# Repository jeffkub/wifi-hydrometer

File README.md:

# wifi-hydrometer
A WiFi-enabled hydrometer and temperature sensor using a ESP8266.  Concept taken from [iSpindel](https://github.com/universam1/iSpindel) and miniturized to fit inside a standard size soda bottle perform.

# Licensing
Design is based on the Adafruit Feather ESP8266 HUZZAH.  
For more details, check out the product page at

  * https://www.adafruit.com/product/2821

Adafruit invests time and resources providing this open source design, 
please support Adafruit and open-source hardware by purchasing 
products from Adafruit!

Adapted from a design by Adafruit Industries.  
Creative Commons Attribution, Share-Alike license, check license.txt for more information
All text above must be included in any redistribution

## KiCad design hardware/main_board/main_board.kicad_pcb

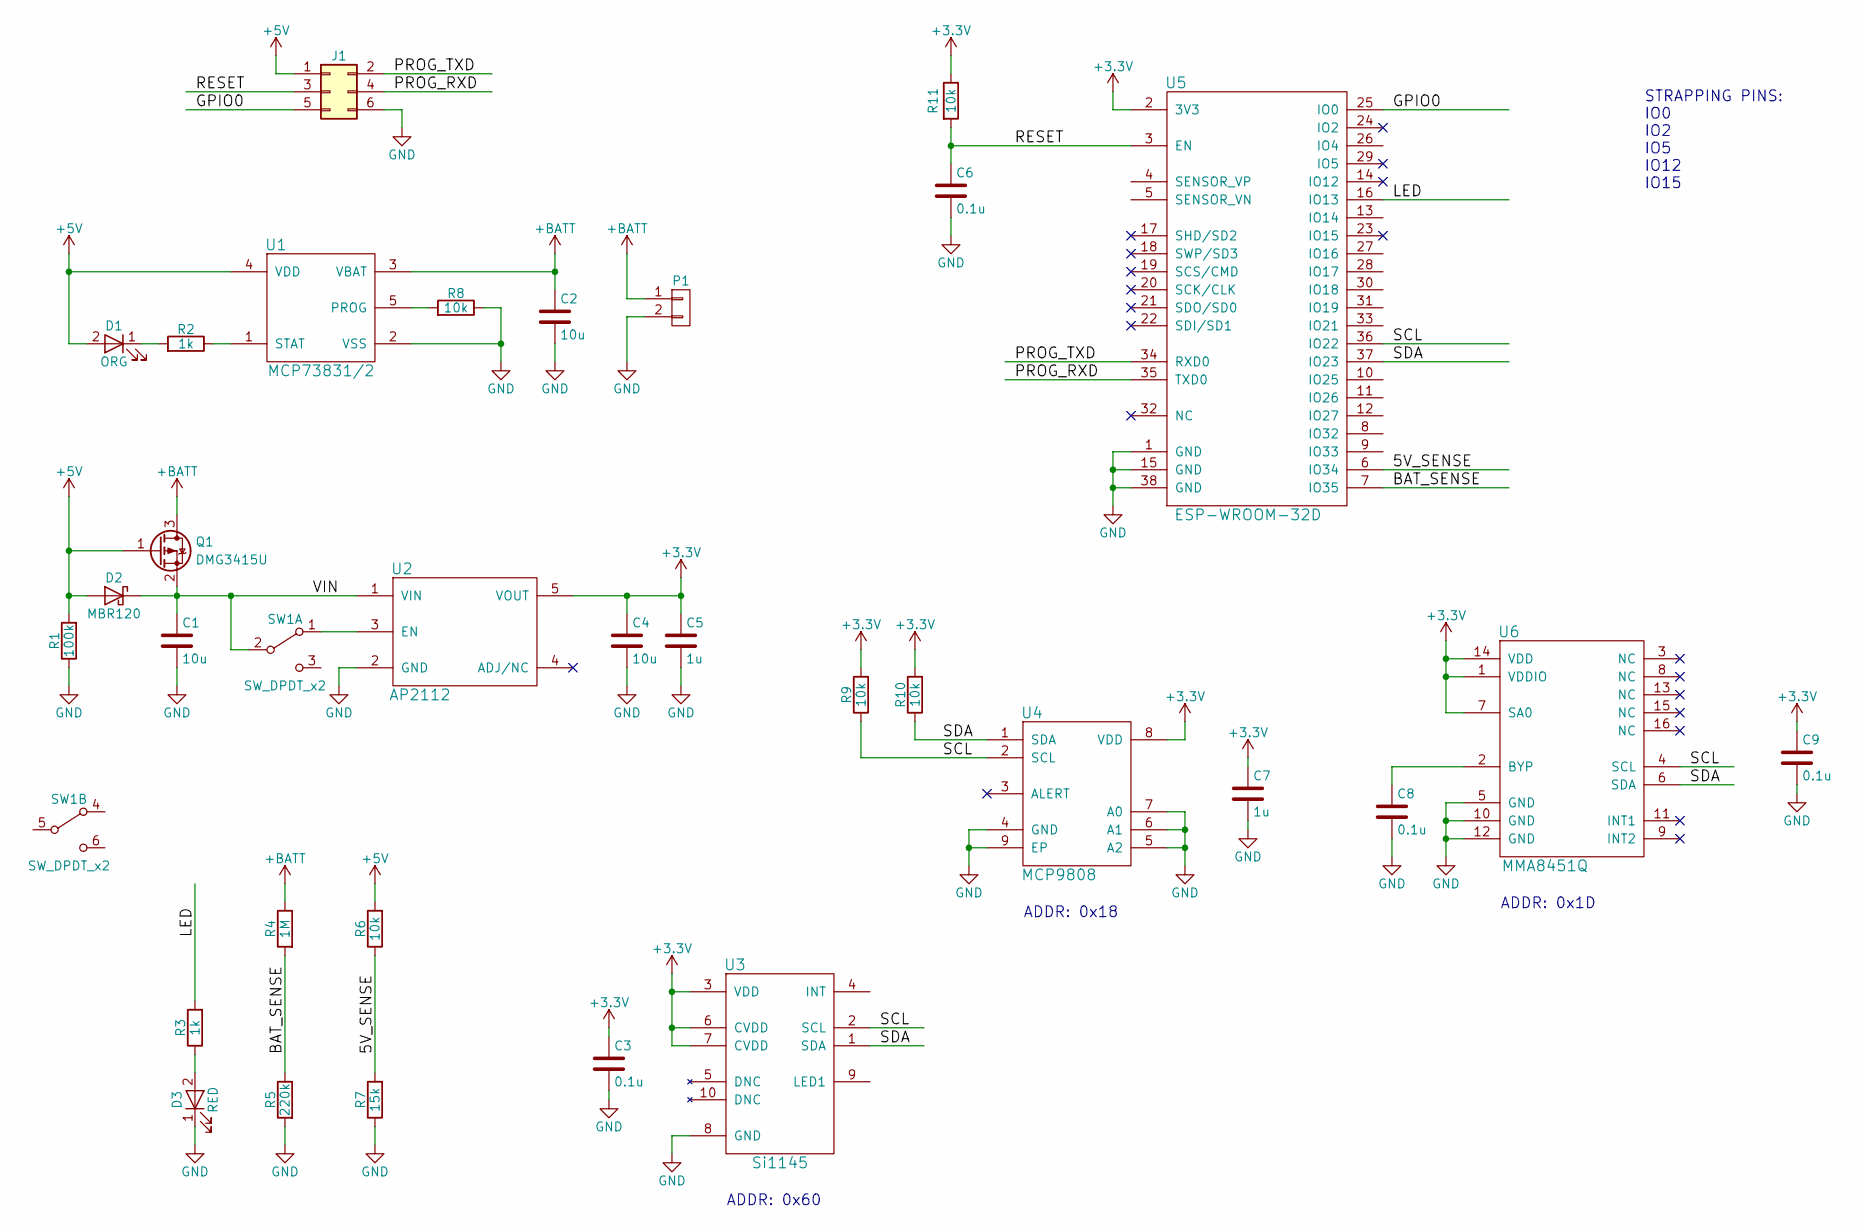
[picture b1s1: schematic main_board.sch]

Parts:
C1, C2, C4: 10u; C_0805; Part 311-1460-1-ND
C3, C6, C8, C9: 0.1u; C_0603; Part 311-1344-1-ND
C5, C7: 1u; C_0603; Part 311-1444-1-ND
D1: ORG; LED_0603; Part 160-1434-1-ND
D2: MBR120; SOD-123FL; Part MBR120VLSFT3GOSCT-ND
D3: RED; LED_0603; Part 160-1447-1-ND
J1: eConn_02x03_Odd_Even; Socket_Strip_Angled_2x03_Pitch2.54mm; Part S5556-ND
P1: CONN_01X02; S2B-PH-SM4-TB(LF)(SN); Part 455-1749-1-ND
Q1: DMG3415U; SOT-23; Part DMG3415UDICT-ND
R1: 100k; R_0603; Part 311-100KHRCT-ND
R2, R3: 1k; R_0603; Part 311-1.00KHRCT-ND
R4: 1M; R_0603; Part 311-1.00MHRCT-ND
R5: 220k; R_0603; Part 311-220KHRCT-ND
R6, R8, R9, R10, R11: 10k; R_0603; Part 311-10.0KHRCT-ND
R7: 15k; R_0603; Part 311-15.0KHRCT-ND
SW1: SW_DPDT_x2; CL-SB-22A; Part 563-1340-1-ND
U1: MCP73831/2; SOT-23-5; Part MCP73831T-2ACI/OTCT-ND
U2: AP2112; SOT-23-5; Part AP2112K-3.3TRG1DICT-ND
U3: Si1145; Part 336-2622-1-ND
U4: MCP9808; DFN-8-1EP_3x2mm_Pitch0.5mm; Part MCP9808T-E/MCCT-ND
U5: ESP-WROOM-32D; ESP32-WROOM; Part 1528-1801-ND
U6: MMA8451Q; Part MMA8451QR1CT-ND

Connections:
+3V3: C3.1, C4.1, C5.1, C7.1, C9.1, R9.2, R10.2, R11.1, U2.5 (VOUT), U3.3 (VDD), U3.6 (CVDD), U3.7 (CVDD), U4.8 (VDD), U5.2 (3V3), U6.1 (VDDIO), U6.7 (SA0), U6.14 (VDD)
+5V: D1.2 (A), D2.2 (A), J1.1, Q1.1 (G), R1.2, R6.2, U1.4 (VDD)
+BATT: C2.1, P1.1, Q1.3 (D), R4.1, U1.3 (VBAT)
/5V_SENSE: R6.1, R7.2, U5.6 (IO34)
/BAT_SENSE: R4.2, R5.1, U5.7 (IO35)
/GPIO0: J1.5, U5.25 (IO0)
/LED: R3.2, U5.16 (IO13)
/PROG_RXD: J1.4, U5.35 (TXD0)
/PROG_TXD: J1.2, U5.34 (RXD0)
/RESET: C6.1, J1.3, R11.2, U5.3 (EN)
/SCL: R9.1, U3.2 (SCL), U4.2 (SCL), U5.36 (IO22), U6.4 (SCL)
/SDA: R10.1, U3.1 (SDA), U4.1 (SDA), U5.37 (IO23), U6.6 (SDA)
/VIN: C1.1, D2.1 (K), Q1.2 (S), SW1.2 (B), U2.1 (VIN)
GND: C1.2, C2.2, C3.2, C4.2, C5.2, C6.2, C7.2, C8.2, C9.2, D3.1 (K), J1.6, P1.2, R1.1, R5.2, R7.1, R8.1, U1.2 (VSS), U2.2 (GND), U3.8 (GND), U4.4 (GND), U4.5 (A2), U4.6 (A1), U4.7 (A0), U4.9 (EP), U5.1 (GND), U5.15 (GND), U5.38 (GND), U6.5 (GND), U6.10 (GND), U6.12 (GND)
unnamed: C8.1, U6.2 (BYP)
unnamed: D1.1 (K), R2.2
unnamed: D3.2 (A), R3.1
unnamed: R2.1, U1.1 (STAT)
unnamed: R8.2, U1.5 (PROG)
unnamed: SW1.1 (A), U2.3 (EN)

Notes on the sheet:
STRAPPING PINS: IO0 IO2 IO5 IO12 IO15
ADDR: 0x60
ADDR: 0x1D
ADDR: 0x18

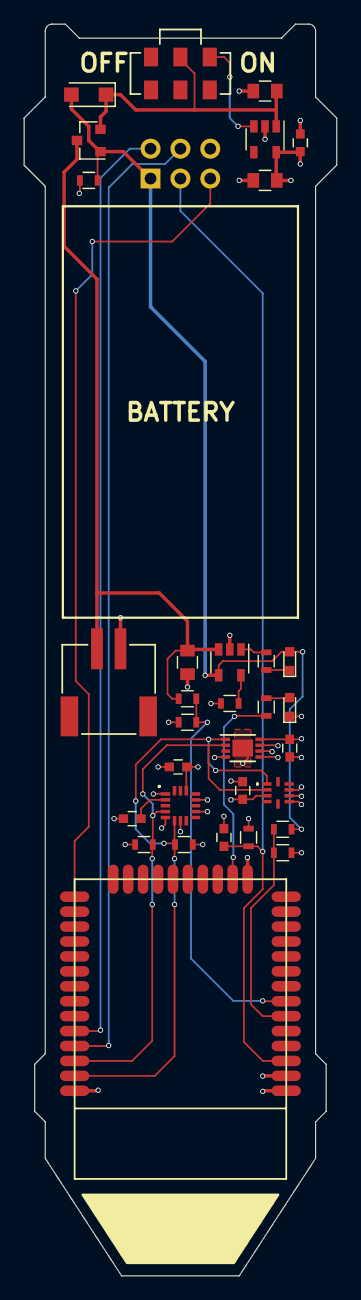
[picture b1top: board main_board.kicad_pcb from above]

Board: 4 copper layers, 26.6 x 106.5 mm, 33 parts (1 on the bottom side), 20 nets.

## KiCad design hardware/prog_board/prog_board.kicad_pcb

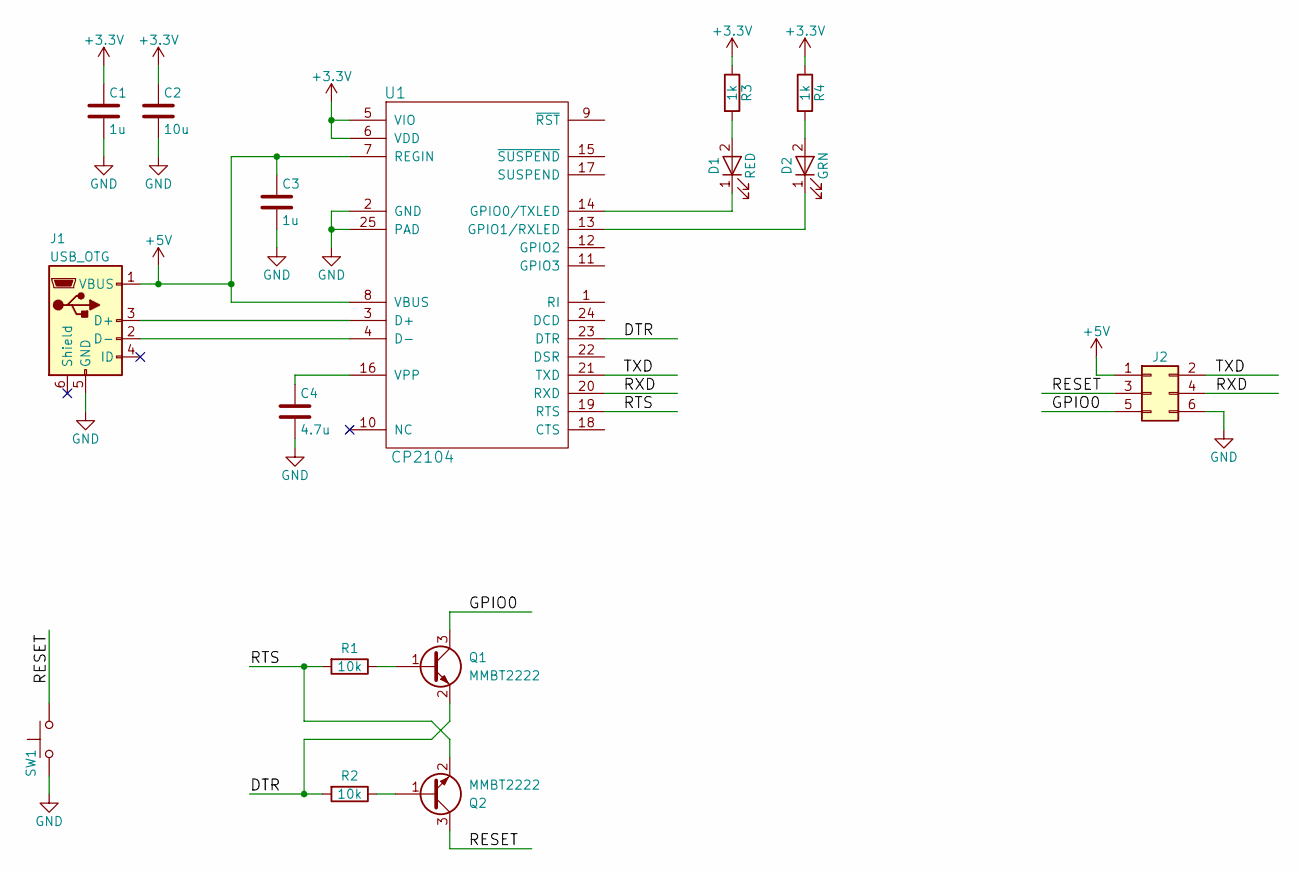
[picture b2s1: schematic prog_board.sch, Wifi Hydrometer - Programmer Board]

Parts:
C1, C3: 1u; C_0603; Part 311-1444-1-ND
C2: 10u; C_0805; Part 311-1460-1-ND
C4: 4.7u; C_0603; Part 311-1455-1-ND
D1: RED; LED_0603; Part 160-1447-1-ND
D2: GRN; LED_0603; Part 160-1435-1-ND
J1: USB_OTG; 10118192; Part 609-4613-1-ND
J2: Conn_02x03_Odd_Even; Pin_Header_Angled_2x03_Pitch2.54mm; Part S2111E-03-ND
Q1, Q2: MMBT2222; SOT-23; Part MMBT2222ALT1GOSCT-ND
R1, R2: 10k; R_0603; Part 311-10.0KHRCT-ND
R3, R4: 1k; R_0603; Part 311-1.00KHRCT-ND
SW1: SW_Push; KMR7; Part CKN10689CT-ND
U1: CP2104; QFN-24-1EP_4x4mm_Pitch0.5mm; Part 336-2008-5-ND

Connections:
+3V3: C1.1, C2.1, R3.1, R4.1, U1.5 (VIO), U1.6 (VDD)
+5V: C3.1, J1.1 (VBUS), J2.1, U1.7 (REGIN), U1.8 (VBUS)
/DTR: Q1.2 (E), R2.2, U1.23 (DTR)
/GPIO0: J2.5, Q1.3 (C)
/RESET: J2.3, Q2.3 (C), SW1.1
/RTS: Q2.2 (E), R1.2, U1.19 (RTS)
/RXD: J2.4, U1.20 (RXD)
/TXD: J2.2, U1.21 (TXD)
GND: C1.2, C2.2, C3.2, C4.2, J1.5 (GND), J2.6, SW1.2, U1.2 (GND), U1.25 (PAD)
unnamed: C4.1, U1.16 (VPP)
unnamed: D1.1 (K), U1.14 (GPIO0/TXLED)
unnamed: D1.2 (A), R3.2
unnamed: D2.1 (K), U1.13 (GPIO1/RXLED)
unnamed: D2.2 (A), R4.2
unnamed: J1.2 (D-), U1.4 (D-)
unnamed: J1.3 (D+), U1.3 (D+)
unnamed: Q1.1 (B), R1.1
unnamed: Q2.1 (B), R2.1

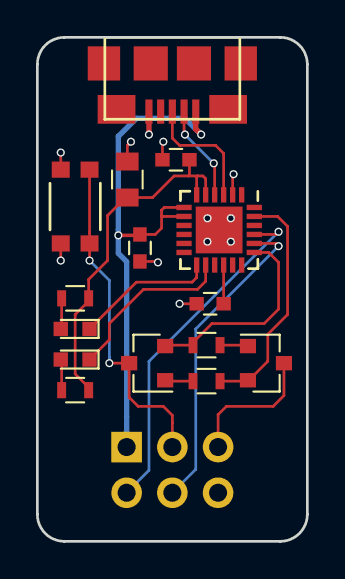
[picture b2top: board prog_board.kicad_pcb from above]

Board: 2 copper layers, 15.0 x 28.0 mm, 16 parts (1 on the bottom side), 18 nets.

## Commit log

2017-03-25 Moved config into header file. Updated PCB image
2017-12-30 Separating design into main and programmer boards
2017-12-30 Moved components to programmer board
2017-12-30 Working on schematic
2017-12-30 Working on layout
2017-12-31 Changed board size to use with new tubes
2018-01-01 Finished routing programming board
2018-01-12 Updated PCB board outline for new tube
2018-01-13 Working on component placement
2018-01-13 Added UV sensor. Working on layout
2018-01-14 Finished routing board
2018-01-15 Minor changes to BOM
2018-02-05 Switched to PlatformIO
2018-02-06 Switched MQTT library
2018-02-06 Removed data struct, using json class instead
2018-02-07 Working on code
2018-02-09 Create driver class for MMA8451 with ability to go into suspend/active modes
2018-02-10 Cleaned up mma8451 driver code
2018-02-10 Created driver class for temperature sensor
2018-02-11 Implemented MCP9808 temp sensor driver
2018-02-11 Created a Sensor base class. Working on SI1145 light sensor driver
2018-02-12 Working on SI1145 light sensor driver
2018-02-13 WWorking on SI1145 light sensor driver
2018-02-13 Sensors are now initialized on first boot only
2018-03-31 Switched to mqtt server on raspberry pi
2018-03-31 Adding python script to log mqtt data
2018-03-31 Adding gitignore
2018-03-31 Reorganizing mqtt topics
2018-03-31 Added session column to database
2018-03-31 Cleaning up logger script
2018-03-31 Added pidfile
2018-03-31 Switched to daemonize library
2018-03-31 Minor cleanup
2018-04-02 Created flask project structure
2018-04-03 Showing all log entries for a device
2018-04-03 Implemented mqtt subscription
2018-04-04 Now logging mqtt messages in web application
2018-04-04 Implemented rotating log file
2018-04-04 Moved mqtt topic string to a constant
2018-04-05 Added requirements.txt
2018-04-05 Implemented index and device page
2018-04-05 Removed old logger program
2018-04-05 Added gunicorn requirement
2018-04-05 Moved publish test script to tools directory
2018-04-09 Added battery voltage chart
